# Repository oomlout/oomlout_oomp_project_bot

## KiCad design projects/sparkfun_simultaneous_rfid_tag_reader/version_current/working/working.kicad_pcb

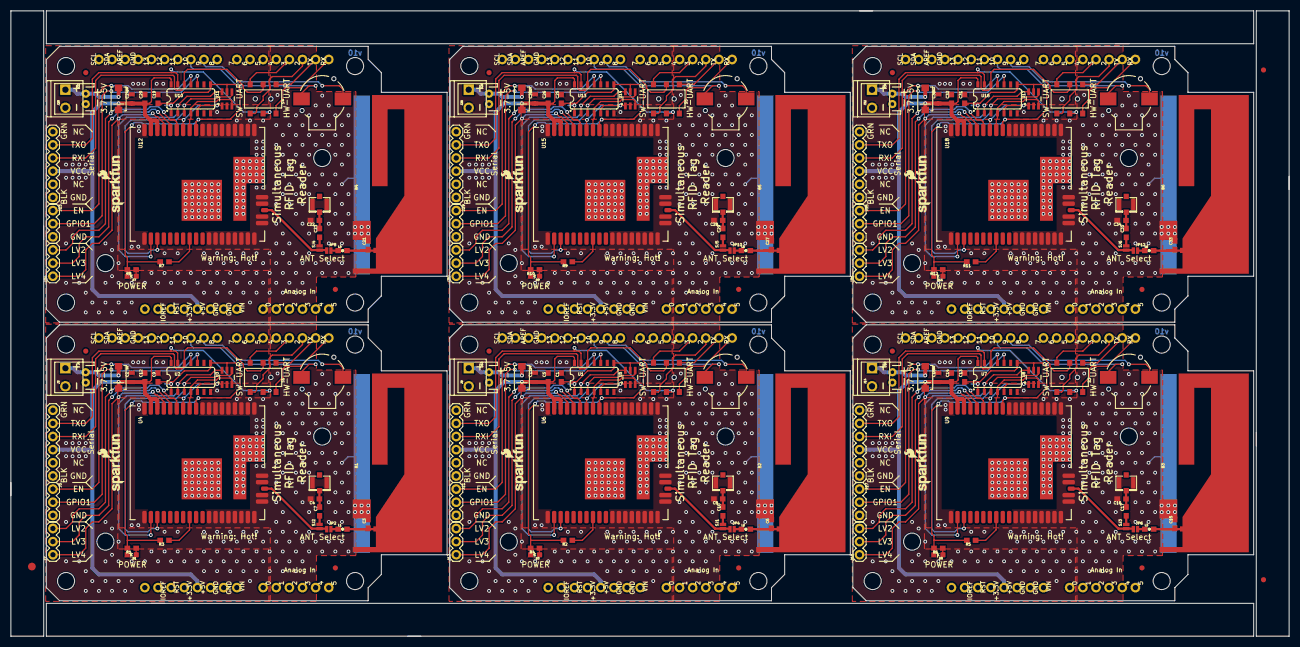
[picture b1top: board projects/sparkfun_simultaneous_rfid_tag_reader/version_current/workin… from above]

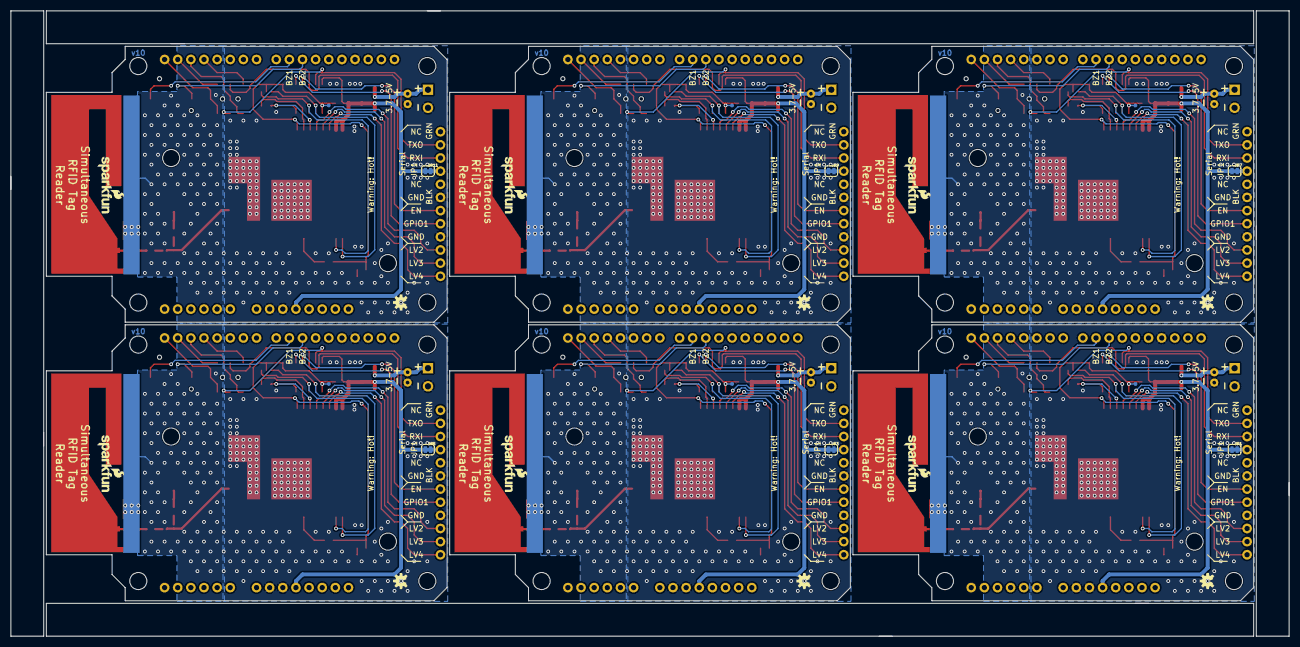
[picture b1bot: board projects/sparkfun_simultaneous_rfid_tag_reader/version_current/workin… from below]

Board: 2 copper layers, 247.1 x 120.9 mm, 237 parts (24 on the bottom side), 174 nets.

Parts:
B1, B2, B3, B4, B5, B6: ARDUINO_UNO_SHIELD; UNO_R3_SHIELD
C1, C5, C9, C12, C13, C14, C19, C20, C25, C26, C31, C32: 0.1uF; 0603
C2, C11, C18, C24, C30, C36: 10uF; 0805
C3, C6, C15, C21, C27, C33: DNP; 0603
C4, C7, C8, C10, C16, C17, C22, C23, C28, C29, C34, C35: TBD; 0603
D1, D3, D5, D7, D9, D11: RED; LED-0603
D2, D4, D6, D8, D10, D12: B340A; SMA-DIODE
E1, E2, E3, E4, E5, E6: Trace Antenna; 915MHZ_ANTENNA_TRIMBLE
E$1: FIDUCIAL-1.5X3
E$7, E$8: FIDUCIAL-1X2
FID1, FID2, FID3, FID4, FID5, FID6, FID7, FID8, FID9, FID10, FID11, FID12: FIDUCIAL1X2; FIDUCIAL-1X2
J1, J2, J13, J19, J25, J31: FTDI; 1X06
J3, J8, J14, J20, J26, J32: JST; JST-2-PTH
J4, J9, J15, J21, J27, J33: U.FL
J5, J11, J17, J23, J29, J35: Extra; 1X03
J6, J10, J16, J22, J28, J34: Screw Terminal; SCREWTERMINAL-3.5MM-2
J7, J12, J18, J24, J30, J36: GPIOs; 1X03
JP1, JP3, JP5, JP7, JP9, JP11: SMT-JUMPER_2_NC_TRACE_SILK
JP2, JP4, JP6, JP8, JP10, JP12: SJ1; SMT-JUMPER_2_NO_NO-SILK
L1, L2, L3, L4, L5, L6: 3.9nH; 0603
LOGO1, LOGO3, LOGO4, LOGO6, LOGO7, LOGO9, LOGO10, LOGO12, LOGO13, LOGO15, LOGO16, LOGO18: SFE_LOGO_NAME_FLAME.1_INCH; SFE_LOGO_NAME_FLAME_.1
LOGO2, LOGO5, LOGO8, LOGO11, LOGO14, LOGO17: OSHW-LOGOS; OSHW-LOGO-S
R1, R2, R3, R4, R5, R6, R7, R8, R9, R10, R11, R12: 1k; 0603
S1, S2, S3, S4, S5, S6: Serial Select; SWITCH_DPDT_SMD_AYZ0202
SG1, SG2, SG3, SG4, SG5, SG6: Buzzer; BUZZER-CCV
SJ1, SJ2, SJ3, SJ4, SJ5, SJ6: SMT-JUMPER_2_NO_NO-SILK
STANDOFF1, STANDOFF2, STANDOFF3, STANDOFF4, STANDOFF5, STANDOFF6, STANDOFF7, STANDOFF8, STANDOFF9, STANDOFF10, STANDOFF11, STANDOFF12, STANDOFF13, STANDOFF14, STANDOFF15, STANDOFF16, STANDOFF17, STANDOFF18, STANDOFF19, STANDOFF20, STANDOFF21, STANDOFF22, STANDOFF23, STANDOFF24, STANDOFF25, STANDOFF26, STANDOFF27, STANDOFF28, STANDOFF29, STANDOFF30, STANDOFF31, STANDOFF32, STANDOFF33, STANDOFF34, STANDOFF35, STANDOFF36: STAND-OFF
TP1, TP2, TP3, TP4, TP5, TP6: PAD.03X.03
U1, U2, U7, U10, U13, U16: TXB0104; SO14
U3, U5, U8, U11, U14, U17: ESD Diode; SOT-23-6
U4, U6, U9, U12, U15, U18: Nano; NANO_MODULE

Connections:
3.3V: C9.1, R1.2, R3.2, TP1.P$1, U2.1, U2.8, U3.5, U4.10
3.3V1: C1.1, R2.2, R4.2, TP2.P$1, U1.1, U1.8, U5.5, U6.10
3.3V2: C13.1, R5.2, R6.2, TP3.P$1, U7.1, U7.8, U8.5, U9.10
3.3V3: C19.1, R7.2, R8.2, TP4.P$1, U10.1, U10.8, U11.5, U12.10
3.3V4: C25.1, R9.2, R10.2, TP5.P$1, U13.1, U13.8, U14.5, U15.10
3.3V5: C31.1, R11.2, R12.2, TP6.P$1, U16.1, U16.8, U17.5, U18.10
ANT1: JP4.1, SJ1.1, U6.39
ANT2: JP6.1, SJ3.1, U9.39
ANT3: JP2.1, SJ2.1, U4.39
ANT4: JP8.1, SJ4.1, U12.39
ANT5: JP10.1, SJ5.1, U15.39
ANT6: JP12.1, SJ6.1, U18.39
ENABLE: J5.1, U2.11
ENABLE1: J11.1, U1.11
ENABLE2: J17.1, U7.11
ENABLE3: J23.1, U10.11
ENABLE4: J29.1, U13.11
ENABLE5: J35.1, U16.11
ENABLE-LV: U2.4, U3.3, U4.11
ENABLE-LV1: U1.4, U5.3, U6.11
ENABLE-LV2: U7.4, U8.3, U9.11
ENABLE-LV3: U10.4, U11.3, U12.11
ENABLE-LV4: U13.4, U14.3, U15.11
ENABLE-LV5: U16.4, U17.3, U18.11
GND: B1.GND@0, B1.GND@1, B1.GND@2, C2.2, C3.2, C4.2, C9.2, C12.2, D1.C, E1.GND@1, E1.GND@2, E1.GND@3, J2.1, J3.1, J4.P$1, J4.P$2, J5.3, J6.2, U2.7, U3.2, U4.1, U4.2, U4.3, U4.4, U4.5, U4.6, U4.7, U4.8, U4.9, U4.18, U4.19, U4.29, U4.30, U4.31, U4.32, U4.33, U4.34, U4.35, U4.36, U4.37, U4.38, U4.40, U4.41, U4.GND_PAD2
GND1: B2.GND@0, B2.GND@1, B2.GND@2, C1.2, C5.2, C6.2, C8.2, C11.2, D3.C, E2.GND@1, E2.GND@2, E2.GND@3, J1.1, J8.1, J9.P$1, J9.P$2, J10.2, J11.3, U1.7, U5.2, U6.1, U6.2, U6.3, U6.4, U6.5, U6.6, U6.7, U6.8, U6.9, U6.18, U6.19, U6.29, U6.30, U6.31, U6.32, U6.33, U6.34, U6.35, U6.36, U6.37, U6.38, U6.40, U6.41, U6.GND_PAD2
GND2: B3.GND@0, B3.GND@1, B3.GND@2, C13.2, C14.2, C15.2, C16.2, C18.2, D5.C, E3.GND@1, E3.GND@2, E3.GND@3, J13.1, J14.1, J15.P$1, J15.P$2, J16.2, J17.3, U7.7, U8.2, U9.1, U9.2, U9.3, U9.4, U9.5, U9.6, U9.7, U9.8, U9.9, U9.18, U9.19, U9.29, U9.30, U9.31, U9.32, U9.33, U9.34, U9.35, U9.36, U9.37, U9.38, U9.40, U9.41, U9.GND_PAD2
GND3: B4.GND@0, B4.GND@1, B4.GND@2, C19.2, C20.2, C21.2, C22.2, C24.2, D7.C, E4.GND@1, E4.GND@2, E4.GND@3, J19.1, J20.1, J21.P$1, J21.P$2, J22.2, J23.3, U10.7, U11.2, U12.1, U12.2, U12.3, U12.4, U12.5, U12.6, U12.7, U12.8, U12.9, U12.18, U12.19, U12.29, U12.30, U12.31, U12.32, U12.33, U12.34, U12.35, U12.36, U12.37, U12.38, U12.40, U12.41, U12.GND_PAD2
GND4: B5.GND@0, B5.GND@1, B5.GND@2, C25.2, C26.2, C27.2, C28.2, C30.2, D9.C, E5.GND@1, E5.GND@2, E5.GND@3, J25.1, J26.1, J27.P$1, J27.P$2, J28.2, J29.3, U13.7, U14.2, U15.1, U15.2, U15.3, U15.4, U15.5, U15.6, U15.7, U15.8, U15.9, U15.18, U15.19, U15.29, U15.30, U15.31, U15.32, U15.33, U15.34, U15.35, U15.36, U15.37, U15.38, U15.40, U15.41, U15.GND_PAD2
GND5: B6.GND@0, B6.GND@1, B6.GND@2, C31.2, C32.2, C33.2, C34.2, C36.2, D11.C, E6.GND@1, E6.GND@2, E6.GND@3, J31.1, J32.1, J33.P$1, J33.P$2, J34.2, J35.3, U16.7, U17.2, U18.1, U18.2, U18.3, U18.4, U18.5, U18.6, U18.7, U18.8, U18.9, U18.18, U18.19, U18.29, U18.30, U18.31, U18.32, U18.33, U18.34, U18.35, U18.36, U18.37, U18.38, U18.40, U18.41, U18.GND_PAD2
GPIO1: J5.2, U2.10
GPIO1-LV: U2.5, U3.1, U4.12
GPIO1-LV1: U1.5, U5.1, U6.12
GPIO1-LV2: U7.5, U8.1, U9.12
GPIO1-LV3: U10.5, U11.1, U12.12
GPIO1-LV4: U13.5, U14.1, U15.12
GPIO1-LV5: U16.5, U17.1, U18.12
GPIO2: J11.2, U1.10
GPIO2-LV: J7.3, U4.13
GPIO2-LV1: J12.3, U6.13
GPIO2-LV2: J18.3, U9.13
GPIO2-LV3: J24.3, U12.13
GPIO2-LV4: J30.3, U15.13
GPIO2-LV5: J36.3, U18.13
GPIO3: J17.2, U7.10
GPIO3-LV: J7.2, U4.14
GPIO3-LV1: J12.2, U6.14
GPIO3-LV2: J18.2, U9.14
GPIO3-LV3: J24.2, U12.14
GPIO3-LV4: J30.2, U15.14
GPIO3-LV5: J36.2, U18.14
GPIO4: J23.2, U10.10
GPIO4-LV: J7.1, U4.15
GPIO4-LV1: J12.1, U6.15
GPIO4-LV2: J18.1, U9.15
GPIO4-LV3: J24.1, U12.15
GPIO4-LV4: J30.1, U15.15
GPIO4-LV5: J36.1, U18.15
GPIO5: J29.2, U13.10
GPIO6: J35.2, U16.10
unnamed: C3.1, E1.ANT, L1.2
unnamed: JP2.2, L1.1
unnamed: C7.1, SJ2.2
unnamed: R3.1, U4.26
unnamed: C4.1, C7.2, J4.P$3
unnamed: D1.A, R1.1
unnamed: J2.3, JP1.2
unnamed: B1.RX, S1.1
unnamed: B1.TX, S1.4
unnamed: B1.D9, SG1.+
unnamed: D2.A, J3.2, J6.1
unnamed: B1.D10, SG1.-
unnamed: R2.1, U6.26
unnamed: B2.RX, S2.1
unnamed: B2.TX, S2.4
unnamed: C6.1, E2.ANT, L2.2
unnamed: JP4.2, L2.1
unnamed: C10.1, SJ1.2
unnamed: C8.1, C10.2, J9.P$3
unnamed: D3.A, R4.1
unnamed: J1.3, JP3.2
unnamed: D4.A, J8.2, J10.1
unnamed: B2.D9, SG2.+
unnamed: B2.D10, SG2.-
unnamed: R5.1, U9.26
unnamed: B3.RX, S3.1
unnamed: B3.TX, S3.4
unnamed: C15.1, E3.ANT, L3.2
unnamed: JP6.2, L3.1
unnamed: C17.1, SJ3.2
unnamed: C16.1, C17.2, J15.P$3
unnamed: D5.A, R6.1
unnamed: J13.3, JP5.2
unnamed: D6.A, J14.2, J16.1
unnamed: B3.D9, SG3.+
unnamed: B3.D10, SG3.-
unnamed: R7.1, U12.26
unnamed: B4.RX, S4.1
unnamed: B4.TX, S4.4
unnamed: C21.1, E4.ANT, L4.2
unnamed: JP8.2, L4.1
unnamed: C23.1, SJ4.2
unnamed: C22.1, C23.2, J21.P$3
unnamed: D7.A, R8.1
unnamed: J19.3, JP7.2
unnamed: D8.A, J20.2, J22.1
unnamed: B4.D9, SG4.+
unnamed: B4.D10, SG4.-
unnamed: R9.1, U15.26
unnamed: B5.RX, S5.1
unnamed: B5.TX, S5.4
unnamed: C27.1, E5.ANT, L5.2
unnamed: JP10.2, L5.1
unnamed: C29.1, SJ5.2
unnamed: C28.1, C29.2, J27.P$3
unnamed: D9.A, R10.1
unnamed: J25.3, JP9.2
unnamed: D10.A, J26.2, J28.1
unnamed: B5.D9, SG5.+
unnamed: B5.D10, SG5.-
unnamed: R11.1, U18.26
unnamed: B6.RX, S6.1
unnamed: B6.TX, S6.4
unnamed: C33.1, E6.ANT, L6.2
unnamed: JP12.2, L6.1
unnamed: C35.1, SJ6.2
unnamed: C34.1, C35.2, J33.P$3
unnamed: D11.A, R12.1
unnamed: J31.3, JP11.2
unnamed: D12.A, J32.2, J34.1
unnamed: B6.D9, SG6.+
unnamed: B6.D10, SG6.-
RXI: J2.4, S1.5, U2.12
RXI1: J1.4, S2.5, U1.12
RXI2: J13.4, S3.5, U7.12
RXI3: J19.4, S4.5, U10.12
RXI4: J25.4, S5.5, U13.12
RXI5: J31.4, S6.5, U16.12
RXI-LV: U2.3, U3.4, U4.21
RXI-LV1: U1.3, U5.4, U6.21
RXI-LV2: U7.3, U8.4, U9.21
RXI-LV3: U10.3, U11.4, U12.21
RXI-LV4: U13.3, U14.4, U15.21
RXI-LV5: U16.3, U17.4, U18.21
SOFT-RX: B1.D2, S1.3
SOFT-RX1: B2.D2, S2.3
SOFT-RX2: B3.D2, S3.3
SOFT-RX3: B4.D2, S4.3
SOFT-RX4: B5.D2, S5.3
SOFT-RX5: B6.D2, S6.3
SOFT-TX: B1.D3, S1.6
SOFT-TX1: B2.D3, S2.6
SOFT-TX2: B3.D3, S3.6
SOFT-TX3: B4.D3, S4.6
SOFT-TX4: B5.D3, S5.6
SOFT-TX5: B6.D3, S6.6
TXO: J2.5, S1.2, U2.13
TXO1: J1.5, S2.2, U1.13
TXO2: J13.5, S3.2, U7.13
TXO3: J19.5, S4.2, U10.13
TXO4: J25.5, S5.2, U13.13
TXO5: J31.5, S6.2, U16.13
TXO-LV: U2.2, U3.6, U4.20
TXO-LV1: U1.2, U5.6, U6.20
TXO-LV2: U7.2, U8.6, U9.20
TXO-LV3: U10.2, U11.6, U12.20
TXO-LV4: U13.2, U14.6, U15.20
TXO-LV5: U16.2, U17.6, U18.20
VCC: B1.5V, C2.1, C12.1, D2.C, JP1.1, U2.14, U4.16, U4.17
VCC1: B2.5V, C5.1, C11.1, D4.C, JP3.1, U1.14, U6.16, U6.17
VCC2: B3.5V, C14.1, C18.1, D6.C, JP5.1, U7.14, U9.16, U9.17
VCC3: B4.5V, C20.1, C24.1, D8.C, JP7.1, U10.14, U12.16, U12.17
VCC4: B5.5V, C26.1, C30.1, D10.C, JP9.1, U13.14, U15.16, U15.17
VCC5: B6.5V, C32.1, C36.1, D12.C, JP11.1, U16.14, U18.16, U18.17

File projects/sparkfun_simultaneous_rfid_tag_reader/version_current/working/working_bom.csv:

"Id";"Designator";"Footprint";"Quantity";"Designation";"Supplier and ref";
1;"STANDOFF33,STANDOFF18,STANDOFF16,STANDOFF35,STANDOFF25,STANDOFF14,STANDOFF5,STANDOFF8,STANDOFF10,STANDOFF26,STANDOFF28,STANDOFF13,STANDOFF7,STANDOFF3,STANDOFF32,STANDOFF9,STANDOFF21,STANDOFF4,STANDOFF20,STANDOFF19,STANDOFF6,STANDOFF24,STANDOFF34,STANDOFF29,STANDOFF23,STANDOFF22,STANDOFF36,STANDOFF2,STANDOFF17,STANDOFF27,STANDOFF31,STANDOFF30,STANDOFF11,STANDOFF1,STANDOFF15,STANDOFF12";"STAND-OFF";36;"STAND-OFF";;;
2;"S3,S5,S4,S6,S1,S2";"SWITCH_DPDT_SMD_AYZ0202";6;"Serial Select";;;
3;"SJ4,SJ1,SJ3,SJ2,SJ5,SJ6";"SMT-JUMPER_2_NO_NO-SILK";6;"";;;
4;"FID10,FID2,FID6,FID11,FID7,FID12,FID5,FID9,FID8,FID1,FID3,FID4";"FIDUCIAL-1X2";12;"FIDUCIAL1X2";;;
5;"C2,C24,C11,C30,C36,C18";"0805";6;"10uF";;;
6;"C26,C12,C5,C20,C19,C1,C14,C31,C9,C25,C13,C32";"0603";12;"0.1uF";;;
7;"J33,J9,J15,J4,J21,J27";"U.FL";6;"U.FL";;;
8;"C8,C17,C10,C29,C7,C34,C23,C4,C22,C16,C28,C35";"0603";12;"TBD";;;
9;"J30,J24,J7,J12,J36,J18";"1X03";6;"GPIOs";;;
10;"J14,J26,J32,J3,J20,J8";"JST-2-PTH";6;"JST";;;
11;"R6,R1,R11,R8,R7,R3,R4,R10,R9,R2,R5,R12";"0603";12;"1k";;;
12;"C15,C33,C21,C3,C6,C27";"0603";6;"DNP";;;
13;"U10,U16,U13,U7,U2,U1";"SO14";6;"TXB0104";;;
14;"J25,J13,J1,J2,J19,J31";"1X06";6;"FTDI";;;
15;"JP2,JP4,JP6,JP10,JP12,JP8";"SMT-JUMPER_2_NO_NO-SILK";6;"SJ1";;;
16;"B6,B3,B2,B4,B5,B1";"UNO_R3_SHIELD";6;"ARDUINO_UNO_SHIELD";;;
17;"LOGO16,LOGO10,LOGO7,LOGO13,LOGO1,LOGO4,LOGO9,LOGO6,LOGO15,LOGO12,LOGO3,LOGO18";"SFE_LOGO_NAME_FLAME_.1";12;"SFE_LOGO_NAME_FLAME.1_INCH";;;
18;"D9,D5,D11,D1,D7,D3";"LED-0603";6;"RED";;;
19;"E5,E2,E6,E1,E3,E4";"915MHZ_ANTENNA_TRIMBLE";6;"Trace Antenna";;;
20;"D8,D10,D2,D4,D12,D6";"SMA-DIODE";6;"B340A";;;
21;"J17,J5,J29,J23,J11,J35";"1X03";6;"Extra";;;
22;"L4,L1,L3,L6,L2,L5";"0603";6;"3.9nH";;;
23;"U6,U15,U9,U18,U4,U12";"NANO_MODULE";6;"Nano";;;
24;"E$8,E$7";"FIDUCIAL-1X2";2;"";;;
25;"SG5,SG3,SG1,SG4,SG2,SG6";"BUZZER-CCV";6;"Buzzer";;;
26;"U3,U17,U8,U14,U11,U5";"SOT-23-6";6;"ESD Diode";;;
27;"J22,J16,J34,J10,J28,J6";"SCREWTERMINAL-3.5MM-2";6;"Screw Terminal";;;
28;"E$1";"FIDUCIAL-1.5X3";1;"";;;
29;"LOGO17,LOGO14,LOGO2,LOGO8,LOGO11,LOGO5";"OSHW-LOGO-S";6;"OSHW-LOGOS";;;
30;"TP5,TP2,TP1,TP6,TP4,TP3";"PAD.03X.03";6;"";;;
31;"JP7,JP9,JP1,JP3,JP11,JP5";"SMT-JUMPER_2_NC_TRACE_SILK";6;"";;;

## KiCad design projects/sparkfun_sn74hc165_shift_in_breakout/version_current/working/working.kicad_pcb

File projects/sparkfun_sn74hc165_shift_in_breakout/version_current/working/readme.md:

# SN74HC165-Shift-In-Breakout by sparkfun  
This is a harvested standardized copy of a project from github.  
The original project can be found at:  
https://github.com/sparkfun/SN74HC165-Shift-In-Breakout  
Please consult that link for additional, details, files, and license information.  
Note: It was auto harvested and if the original repo had more than one board file or anything out of the ordinary the files here are likely not representative.

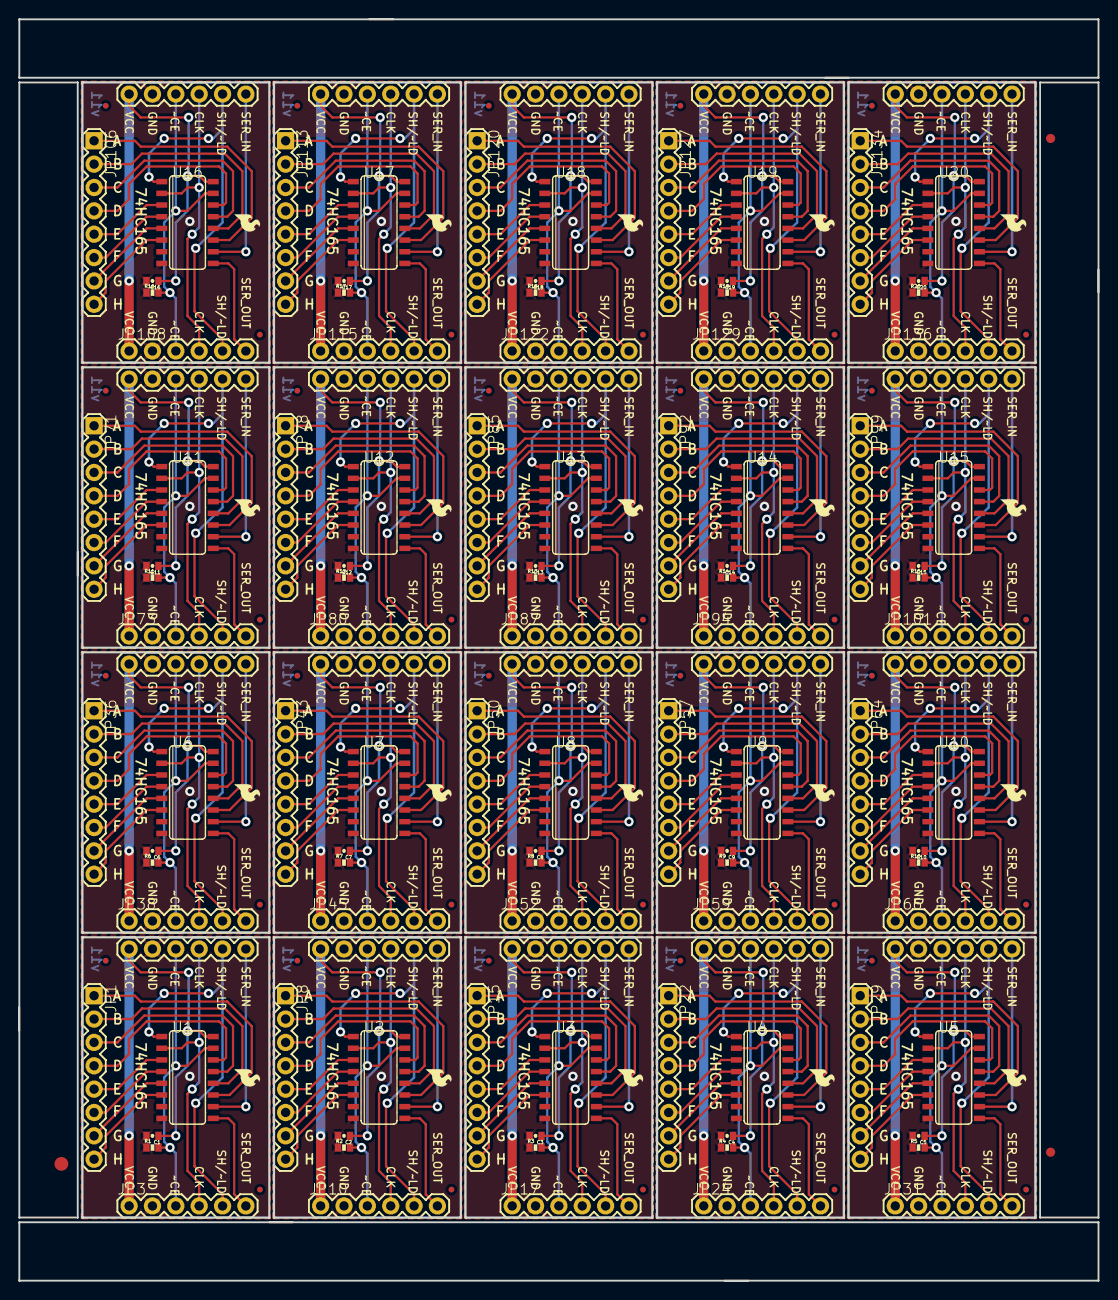
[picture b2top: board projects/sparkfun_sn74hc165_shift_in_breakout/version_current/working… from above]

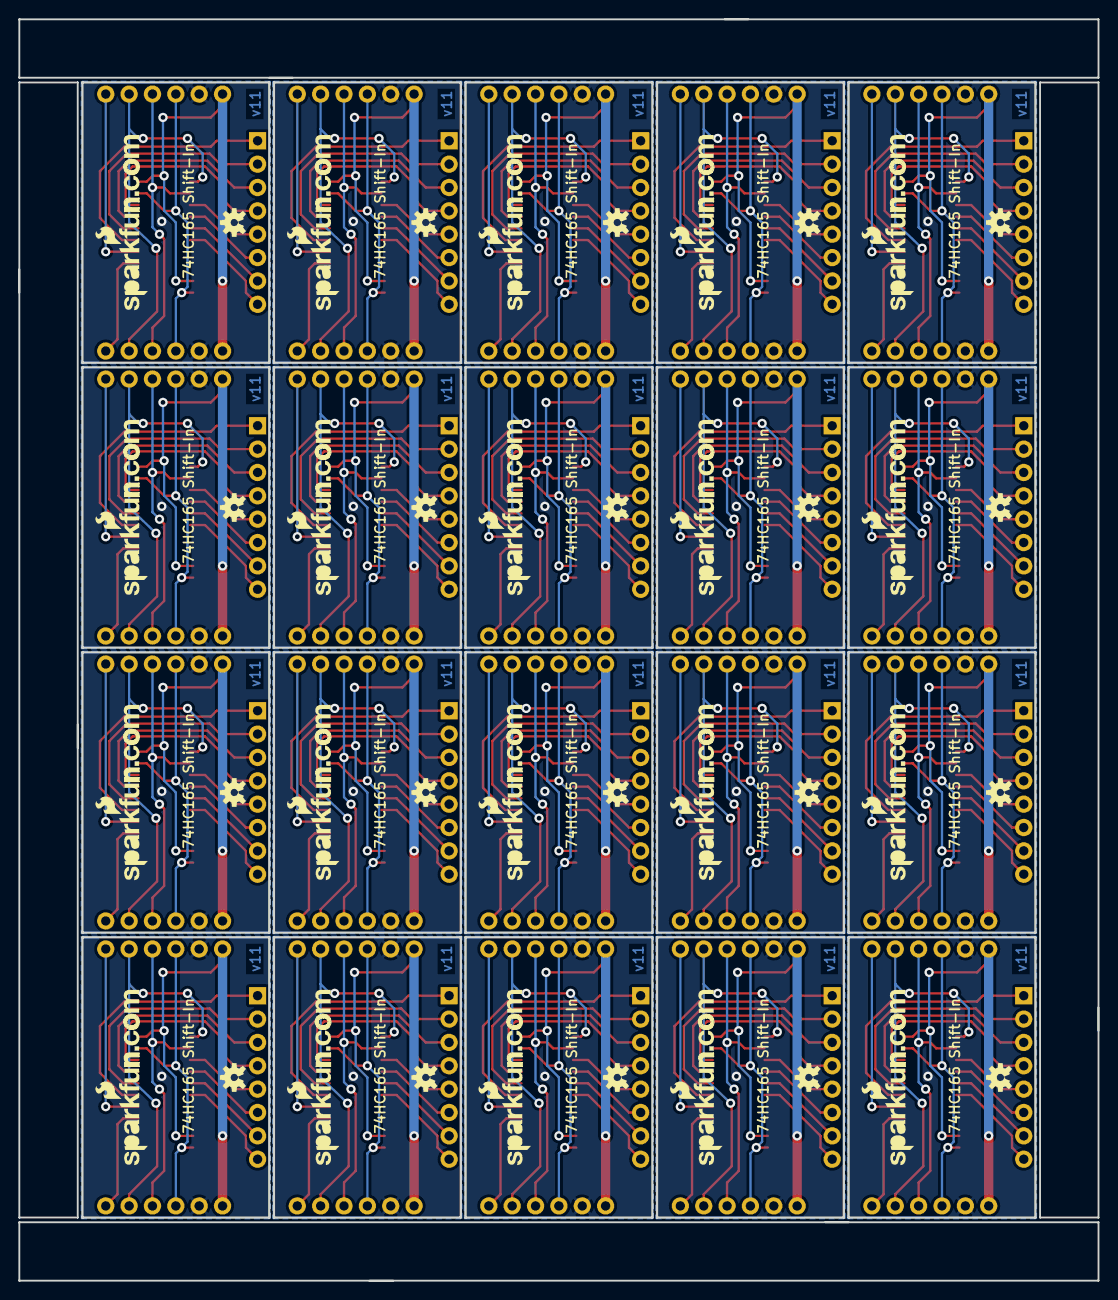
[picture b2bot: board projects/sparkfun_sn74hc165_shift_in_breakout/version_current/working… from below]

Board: 2 copper layers, 117.3 x 137.2 mm, 223 parts (40 on the bottom side), 300 nets.

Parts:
C1, C2, C3, C4, C5, C6, C7, C8, C9, C10, C11, C12, C13, C14, C15, C16, C17, C18, C19, C20: .1uF; 0402-CAP
E$1: FIDUCIAL-1.5X3
E$7, E$8: FIDUCIAL-1X2
JP1, JP8, JP15, JP22, JP29, JP36, JP43, JP50, JP57, JP64, JP71, JP78, JP85, JP92, JP99, JP106, JP113, JP120, JP127, JP134: 1X08
JP2, JP3, JP9, JP10, JP16, JP17, JP23, JP24, JP30, JP31, JP37, JP38, JP44, JP45, JP51, JP52, JP58, JP59, JP65, JP66, JP72, JP73, JP79, JP80, JP86, JP87, JP93, JP94, JP100, JP101, JP107, JP108, JP114, JP115, JP121, JP122, JP128, JP129, JP135, JP136: 1X06
JP4, JP11, JP18, JP25, JP32, JP39, JP46, JP53, JP60, JP67, JP74, JP81, JP88, JP95, JP102, JP109, JP116, JP123, JP130, JP137: LOGO-SFESK; SFE-LOGO-FLAME
JP5, JP12, JP19, JP26, JP33, JP40, JP47, JP54, JP61, JP68, JP75, JP82, JP89, JP96, JP103, JP110, JP117, JP124, JP131, JP138: LOGO-SFENEW; SFE-NEW-WEBLOGO
JP6, JP7, JP13, JP14, JP20, JP21, JP27, JP28, JP34, JP35, JP41, JP42, JP48, JP49, JP55, JP56, JP62, JP63, JP69, JP70, JP76, JP77, JP83, JP84, JP90, JP91, JP97, JP98, JP104, JP105, JP111, JP112, JP118, JP119, JP125, JP126, JP132, JP133, JP139, JP140: FIDUCIALUFIDUCIAL; MICRO-FIDUCIAL
R1, R2, R3, R4, R5, R6, R7, R8, R9, R10, R11, R12, R13, R14, R15, R16, R17, R18, R19, R20: 10k; 0402-RES
U1, U2, U3, U4, U5, U6, U7, U8, U9, U10, U11, U12, U13, U14, U15, U16, U17, U18, U19, U20: 74HC165D; SO16
U$1, U$2, U$3, U$4, U$5, U$6, U$7, U$8, U$9, U$10, U$11, U$12, U$13, U$14, U$15, U$16, U$17, U$18, U$19, U$20: OSHW-LOGOS; OSHW-LOGO-S

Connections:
A: JP1.1, U1.11
A1: JP8.1, U2.11
A2: JP15.1, U3.11
A3: JP22.1, U4.11
A4: JP29.1, U5.11
A5: JP36.1, U6.11
A6: JP43.1, U7.11
A7: JP50.1, U8.11
A8: JP57.1, U9.11
A9: JP64.1, U10.11
A10: JP71.1, U11.11
A11: JP78.1, U12.11
A12: JP85.1, U13.11
A13: JP92.1, U14.11
A14: JP99.1, U15.11
A15: JP106.1, U16.11
A16: JP113.1, U17.11
A17: JP120.1, U18.11
A18: JP127.1, U19.11
A19: JP134.1, U20.11
B: JP1.2, U1.12
B1: JP8.2, U2.12
B2: JP15.2, U3.12
B3: JP22.2, U4.12
B4: JP29.2, U5.12
B5: JP36.2, U6.12
B6: JP43.2, U7.12
B7: JP50.2, U8.12
B8: JP57.2, U9.12
B9: JP64.2, U10.12
B10: JP71.2, U11.12
B11: JP78.2, U12.12
B12: JP85.2, U13.12
B13: JP92.2, U14.12
B14: JP99.2, U15.12
B15: JP106.2, U16.12
B16: JP113.2, U17.12
B17: JP120.2, U18.12
B18: JP127.2, U19.12
B19: JP134.2, U20.12
C: JP1.3, U1.13
C1: JP8.3, U2.13
C2: JP15.3, U3.13
C3: JP22.3, U4.13
C4: JP29.3, U5.13
C5: JP36.3, U6.13
C6: JP43.3, U7.13
C7: JP50.3, U8.13
C8: JP57.3, U9.13
C9: JP64.3, U10.13
C10: JP71.3, U11.13
C11: JP78.3, U12.13
C12: JP85.3, U13.13
C13: JP92.3, U14.13
C14: JP99.3, U15.13
C15: JP106.3, U16.13
C16: JP113.3, U17.13
C17: JP120.3, U18.13
C18: JP127.3, U19.13
C19: JP134.3, U20.13
CLK: JP2.4, JP3.4, U1.2
CLK1: JP9.4, JP10.4, U2.2
CLK2: JP16.4, JP17.4, U3.2
CLK3: JP23.4, JP24.4, U4.2
CLK4: JP30.4, JP31.4, U5.2
CLK5: JP37.4, JP38.4, U6.2
CLK6: JP44.4, JP45.4, U7.2
CLK7: JP51.4, JP52.4, U8.2
CLK8: JP58.4, JP59.4, U9.2
CLK9: JP65.4, JP66.4, U10.2
CLK10: JP72.4, JP73.4, U11.2
CLK11: JP79.4, JP80.4, U12.2
CLK12: JP86.4, JP87.4, U13.2
CLK13: JP93.4, JP94.4, U14.2
CLK14: JP100.4, JP101.4, U15.2
CLK15: JP107.4, JP108.4, U16.2
CLK16: JP114.4, JP115.4, U17.2
CLK17: JP121.4, JP122.4, U18.2
CLK18: JP128.4, JP129.4, U19.2
CLK19: JP135.4, JP136.4, U20.2
D: JP1.4, U1.14
D1: JP8.4, U2.14
D2: JP15.4, U3.14
D3: JP22.4, U4.14
D4: JP29.4, U5.14
D5: JP36.4, U6.14
D6: JP43.4, U7.14
D7: JP50.4, U8.14
D8: JP57.4, U9.14
D9: JP64.4, U10.14
D10: JP71.4, U11.14
D11: JP78.4, U12.14
D12: JP85.4, U13.14
D13: JP92.4, U14.14
D14: JP99.4, U15.14
D15: JP106.4, U16.14
D16: JP113.4, U17.14
D17: JP120.4, U18.14
D18: JP127.4, U19.14
D19: JP134.4, U20.14
E: JP1.5, U1.3
E1: JP8.5, U2.3
E2: JP15.5, U3.3
E3: JP22.5, U4.3
E4: JP29.5, U5.3
E5: JP36.5, U6.3
E6: JP43.5, U7.3
E7: JP50.5, U8.3
E8: JP57.5, U9.3
E9: JP64.5, U10.3
E10: JP71.5, U11.3
E11: JP78.5, U12.3
E12: JP85.5, U13.3
E13: JP92.5, U14.3
E14: JP99.5, U15.3
E15: JP106.5, U16.3
E16: JP113.5, U17.3
E17: JP120.5, U18.3
E18: JP127.5, U19.3
E19: JP134.5, U20.3
F: JP1.6, U1.4
F1: JP8.6, U2.4
F2: JP15.6, U3.4
F3: JP22.6, U4.4
F4: JP29.6, U5.4
F5: JP36.6, U6.4
F6: JP43.6, U7.4
F7: JP50.6, U8.4
F8: JP57.6, U9.4
F9: JP64.6, U10.4
F10: JP71.6, U11.4
F11: JP78.6, U12.4
F12: JP85.6, U13.4
F13: JP92.6, U14.4
F14: JP99.6, U15.4
F15: JP106.6, U16.4
F16: JP113.6, U17.4
F17: JP120.6, U18.4
F18: JP127.6, U19.4
F19: JP134.6, U20.4
G: JP1.7, U1.5
G1: JP8.7, U2.5
G2: JP15.7, U3.5
G3: JP22.7, U4.5
G4: JP29.7, U5.5
G5: JP36.7, U6.5
G6: JP43.7, U7.5
G7: JP50.7, U8.5
G8: JP57.7, U9.5
G9: JP64.7, U10.5
G10: JP71.7, U11.5
G11: JP78.7, U12.5
G12: JP85.7, U13.5
G13: JP92.7, U14.5
G14: JP99.7, U15.5
G15: JP106.7, U16.5
G16: JP113.7, U17.5
G17: JP120.7, U18.5
G18: JP127.7, U19.5
G19: JP134.7, U20.5
GND: C1.2, JP2.2, JP3.2, R1.1, U1.8
GND1: C2.2, JP9.2, JP10.2, R2.1, U2.8
GND2: C3.2, JP16.2, JP17.2, R3.1, U3.8
GND3: C4.2, JP23.2, JP24.2, R4.1, U4.8
GND4: C5.2, JP30.2, JP31.2, R5.1, U5.8
GND5: C6.2, JP37.2, JP38.2, R6.1, U6.8
GND6: C7.2, JP44.2, JP45.2, R7.1, U7.8
GND7: C8.2, JP51.2, JP52.2, R8.1, U8.8
GND8: C9.2, JP58.2, JP59.2, R9.1, U9.8
GND9: C10.2, JP65.2, JP66.2, R10.1, U10.8
GND10: C11.2, JP72.2, JP73.2, R11.1, U11.8
GND11: C12.2, JP79.2, JP80.2, R12.1, U12.8
GND12: C13.2, JP86.2, JP87.2, R13.1, U13.8
GND13: C14.2, JP93.2, JP94.2, R14.1, U14.8
GND14: C15.2, JP100.2, JP101.2, R15.1, U15.8
GND15: C16.2, JP107.2, JP108.2, R16.1, U16.8
GND16: C17.2, JP114.2, JP115.2, R17.1, U17.8
GND17: C18.2, JP121.2, JP122.2, R18.1, U18.8
GND18: C19.2, JP128.2, JP129.2, R19.1, U19.8
GND19: C20.2, JP135.2, JP136.2, R20.1, U20.8
H: JP1.8, U1.6
H1: JP8.8, U2.6
H2: JP15.8, U3.6
H3: JP22.8, U4.6
H4: JP29.8, U5.6
H5: JP36.8, U6.6
H6: JP43.8, U7.6
H7: JP50.8, U8.6
H8: JP57.8, U9.6
H9: JP64.8, U10.6
H10: JP71.8, U11.6
H11: JP78.8, U12.6
H12: JP85.8, U13.6
H13: JP92.8, U14.6
H14: JP99.8, U15.6
H15: JP106.8, U16.6
H16: JP113.8, U17.6
H17: JP120.8, U18.6
H18: JP127.8, U19.6
H19: JP134.8, U20.6
SERIAL_IN: JP2.6, U1.10
SERIAL_IN1: JP9.6, U2.10
SERIAL_IN2: JP16.6, U3.10
SERIAL_IN3: JP23.6, U4.10
SERIAL_IN4: JP30.6, U5.10
SERIAL_IN5: JP37.6, U6.10
SERIAL_IN6: JP44.6, U7.10
SERIAL_IN7: JP51.6, U8.10
SERIAL_IN8: JP58.6, U9.10
SERIAL_IN9: JP65.6, U10.10
SERIAL_IN10: JP72.6, U11.10
SERIAL_IN11: JP79.6, U12.10
SERIAL_IN12: JP86.6, U13.10
SERIAL_IN13: JP93.6, U14.10
SERIAL_IN14: JP100.6, U15.10
SERIAL_IN15: JP107.6, U16.10
SERIAL_IN16: JP114.6, U17.10
SERIAL_IN17: JP121.6, U18.10
SERIAL_IN18: JP128.6, U19.10
SERIAL_IN19: JP135.6, U20.10
SERIAL_OUT: JP3.6, U1.9
SERIAL_OUT1: JP10.6, U2.9
SERIAL_OUT2: JP17.6, U3.9
SERIAL_OUT3: JP24.6, U4.9
SERIAL_OUT4: JP31.6, U5.9
SERIAL_OUT5: JP38.6, U6.9
SERIAL_OUT6: JP45.6, U7.9
SERIAL_OUT7: JP52.6, U8.9
SERIAL_OUT8: JP59.6, U9.9
SERIAL_OUT9: JP66.6, U10.9
SERIAL_OUT10: JP73.6, U11.9
SERIAL_OUT11: JP80.6, U12.9
SERIAL_OUT12: JP87.6, U13.9
SERIAL_OUT13: JP94.6, U14.9
SERIAL_OUT14: JP101.6, U15.9
SERIAL_OUT15: JP108.6, U16.9
SERIAL_OUT16: JP115.6, U17.9
SERIAL_OUT17: JP122.6, U18.9
SERIAL_OUT18: JP129.6, U19.9
SERIAL_OUT19: JP136.6, U20.9
SHIFT/~LOAD1: JP9.5, JP10.5, U2.1
SHIFT/~LOAD2: JP16.5, JP17.5, U3.1
SHIFT/~LOAD3: JP23.5, JP24.5, U4.1
SHIFT/~LOAD4: JP30.5, JP31.5, U5.1
SHIFT/~LOAD5: JP37.5, JP38.5, U6.1
SHIFT/~LOAD6: JP44.5, JP45.5, U7.1
SHIFT/~LOAD7: JP51.5, JP52.5, U8.1
SHIFT/~LOAD8: JP58.5, JP59.5, U9.1
SHIFT/~LOAD9: JP65.5, JP66.5, U10.1
SHIFT/~LOAD10: JP72.5, JP73.5, U11.1
SHIFT/~LOAD11: JP79.5, JP80.5, U12.1
SHIFT/~LOAD12: JP86.5, JP87.5, U13.1
SHIFT/~LOAD13: JP93.5, JP94.5, U14.1
SHIFT/~LOAD14: JP100.5, JP101.5, U15.1
SHIFT/~LOAD15: JP107.5, JP108.5, U16.1
SHIFT/~LOAD16: JP114.5, JP115.5, U17.1
SHIFT/~LOAD17: JP121.5, JP122.5, U18.1
SHIFT/~LOAD18: JP128.5, JP129.5, U19.1
SHIFT/~LOAD19: JP135.5, JP136.5, U20.1
SHIFT/~LOAD: JP2.5, JP3.5, U1.1
VCC: C1.1, JP2.1, JP3.1, U1.16
VCC1: C2.1, JP9.1, JP10.1, U2.16
VCC2: C3.1, JP16.1, JP17.1, U3.16
VCC3: C4.1, JP23.1, JP24.1, U4.16
VCC4: C5.1, JP30.1, JP31.1, U5.16
VCC5: C6.1, JP37.1, JP38.1, U6.16
VCC6: C7.1, JP44.1, JP45.1, U7.16
VCC7: C8.1, JP51.1, JP52.1, U8.16
VCC8: C9.1, JP58.1, JP59.1, U9.16
VCC9: C10.1, JP65.1, JP66.1, U10.16
VCC10: C11.1, JP72.1, JP73.1, U11.16
VCC11: C12.1, JP79.1, JP80.1, U12.16
VCC12: C13.1, JP86.1, JP87.1, U13.16
VCC13: C14.1, JP93.1, JP94.1, U14.16
VCC14: C15.1, JP100.1, JP101.1, U15.16
VCC15: C16.1, JP107.1, JP108.1, U16.16
VCC16: C17.1, JP114.1, JP115.1, U17.16
VCC17: C18.1, JP121.1, JP122.1, U18.16
VCC18: C19.1, JP128.1, JP129.1, U19.16
VCC19: C20.1, JP135.1, JP136.1, U20.16
~CLK_ENABLE1: JP9.3, JP10.3, R2.2, U2.15
~CLK_ENABLE2: JP16.3, JP17.3, R3.2, U3.15
~CLK_ENABLE3: JP23.3, JP24.3, R4.2, U4.15
~CLK_ENABLE4: JP30.3, JP31.3, R5.2, U5.15
~CLK_ENABLE5: JP37.3, JP38.3, R6.2, U6.15
~CLK_ENABLE6: JP44.3, JP45.3, R7.2, U7.15
~CLK_ENABLE7: JP51.3, JP52.3, R8.2, U8.15
~CLK_ENABLE8: JP58.3, JP59.3, R9.2, U9.15
~CLK_ENABLE9: JP65.3, JP66.3, R10.2, U10.15
~CLK_ENABLE10: JP72.3, JP73.3, R11.2, U11.15
~CLK_ENABLE11: JP79.3, JP80.3, R12.2, U12.15
~CLK_ENABLE12: JP86.3, JP87.3, R13.2, U13.15
~CLK_ENABLE13: JP93.3, JP94.3, R14.2, U14.15
~CLK_ENABLE14: JP100.3, JP101.3, R15.2, U15.15
~CLK_ENABLE15: JP107.3, JP108.3, R16.2, U16.15
~CLK_ENABLE16: JP114.3, JP115.3, R17.2, U17.15
~CLK_ENABLE17: JP121.3, JP122.3, R18.2, U18.15
~CLK_ENABLE18: JP128.3, JP129.3, R19.2, U19.15
~CLK_ENABLE19: JP135.3, JP136.3, R20.2, U20.15
~CLK_ENABLE: JP2.3, JP3.3, R1.2, U1.15

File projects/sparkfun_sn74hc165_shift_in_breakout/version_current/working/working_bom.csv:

"Id";"Designator";"Footprint";"Quantity";"Designation";"Supplier and ref";
1;"JP10,JP3,JP59,JP93,JP101,JP52,JP108,JP122,JP65,JP100,JP73,JP17,JP80,JP107,JP38,JP23,JP2,JP44,JP121,JP30,JP24,JP87,JP45,JP51,JP94,JP37,JP16,JP86,JP79,JP135,JP136,JP66,JP128,JP31,JP72,JP114,JP129,JP9,JP115,JP58";"1X06";40;"";;;
2;"JP20,JP21,JP77,JP7,JP27,JP48,JP6,JP63,JP105,JP13,JP97,JP55,JP69,JP104,JP125,JP56,JP111,JP42,JP126,JP84,JP76,JP83,JP112,JP90,JP34,JP91,JP132,JP139,JP62,JP119,JP70,JP98,JP133,JP49,JP35,JP118,JP140,JP28,JP14,JP41";"MICRO-FIDUCIAL";40;"FIDUCIALUFIDUCIAL";;;
3;"JP11,JP102,JP18,JP60,JP46,JP39,JP123,JP137,JP95,JP53,JP74,JP67,JP109,JP32,JP25,JP88,JP130,JP116,JP81,JP4";"SFE-LOGO-FLAME";20;"LOGO-SFESK";;;
4;"R10,R8,R19,R2,R14,R5,R12,R15,R20,R17,R9,R13,R7,R3,R16,R11,R1,R18,R6,R4";"0402-RES";20;"10k";;;
5;"JP127,JP8,JP78,JP64,JP36,JP50,JP15,JP22,JP134,JP57,JP71,JP99,JP92,JP29,JP85,JP120,JP43,JP113,JP1,JP106";"1X08";20;"";;;
6;"C5,C6,C1,C19,C4,C13,C9,C3,C2,C14,C10,C8,C15,C18,C11,C7,C20,C12,C16,C17";"0402-CAP";20;".1uF";;;
7;"E$7,E$8";"FIDUCIAL-1X2";2;"";;;
8;"U17,U20,U8,U16,U6,U15,U10,U12,U11,U19,U2,U3,U5,U13,U9,U7,U18,U1,U4,U14";"SO16";20;"74HC165D";;;
9;"E$1";"FIDUCIAL-1.5X3";1;"";;;
10;"U$18,U$15,U$12,U$16,U$11,U$19,U$13,U$5,U$1,U$9,U$2,U$10,U$4,U$7,U$3,U$17,U$6,U$14,U$20,U$8";"OSHW-LOGO-S";20;"OSHW-LOGOS";;;
11;"JP89,JP19,JP54,JP40,JP117,JP138,JP12,JP96,JP131,JP47,JP33,JP5,JP103,JP75,JP82,JP110,JP124,JP61,JP26,JP68";"SFE-NEW-WEBLOGO";20;"LOGO-SFENEW";;;

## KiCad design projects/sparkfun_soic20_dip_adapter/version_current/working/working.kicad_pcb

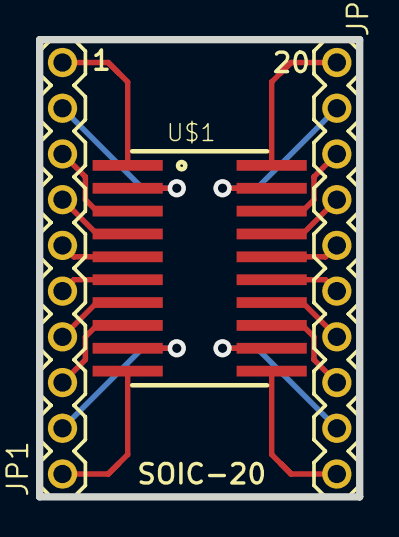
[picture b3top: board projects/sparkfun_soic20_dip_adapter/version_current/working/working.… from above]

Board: 16 copper layers, 17.8 x 25.4 mm, 4 parts (1 on the bottom side), 20 nets.

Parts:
JP1, JP2: M100.1; 1X10
U$1: SOIC_20; SO20W
U$2: LOGO-SFENEW; SFE-NEW-WEBLOGO

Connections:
unnamed: JP1.1, U$1.P$10
unnamed: JP1.2, U$1.P$9
unnamed: JP1.3, U$1.P$8
unnamed: JP1.4, U$1.P$7
unnamed: JP1.5, U$1.P$6
unnamed: JP1.6, U$1.P$5
unnamed: JP1.7, U$1.P$4
unnamed: JP1.8, U$1.P$3
unnamed: JP1.9, U$1.P$2
unnamed: JP1.10, U$1.P$1
unnamed: JP2.1, U$1.P$20
unnamed: JP2.2, U$1.P$19
unnamed: JP2.3, U$1.P$18
unnamed: JP2.4, U$1.P$17
unnamed: JP2.5, U$1.P$16
unnamed: JP2.6, U$1.P$15
unnamed: JP2.7, U$1.P$14
unnamed: JP2.8, U$1.P$13
unnamed: JP2.9, U$1.P$12
unnamed: JP2.10, U$1.P$11

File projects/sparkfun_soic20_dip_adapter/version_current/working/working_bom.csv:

"Id";"Designator";"Footprint";"Quantity";"Designation";"Supplier and ref";
1;"JP2,JP1";"1X10";2;"M100.1";;;
2;"U$1";"SO20W";1;"SOIC_20";;;
3;"U$2";"SFE-NEW-WEBLOGO";1;"LOGO-SFENEW";;;

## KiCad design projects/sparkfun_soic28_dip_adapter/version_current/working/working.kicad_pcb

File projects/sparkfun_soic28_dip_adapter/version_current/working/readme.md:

# SOIC28-DIP_Adapter by sparkfun  
This is a harvested standardized copy of a project from github.  
The original project can be found at:  
https://github.com/sparkfun/SOIC28-DIP_Adapter  
Please consult that link for additional, details, files, and license information.  
Note: It was auto harvested and if the original repo had more than one board file or anything out of the ordinary the files here are likely not representative.

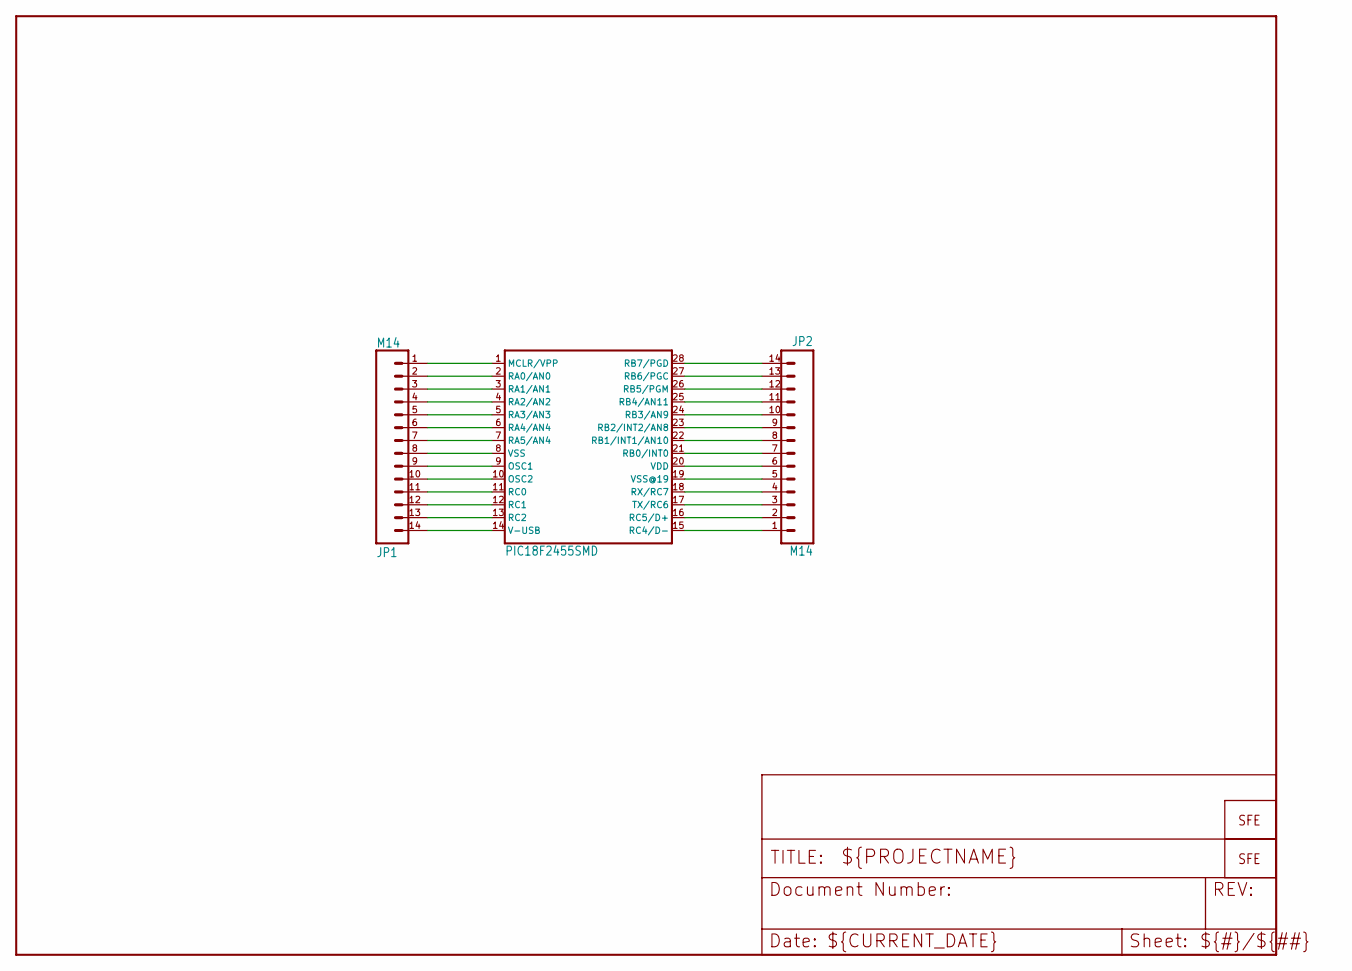
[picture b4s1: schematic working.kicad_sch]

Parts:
JP1, JP2: M14; 1X14
U$1: LOGO-SFESK; SFE-LOGO-FLAME
U$2: LOGO-SFENEW; SFE-NEW-WEBLOGO
U$3: PIC18F2455SMD; SO-28W

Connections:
unnamed: JP1.1, U$3.1 (MCLR/VPP)
unnamed: JP1.2, U$3.2 (RA0/AN0)
unnamed: JP1.3, U$3.3 (RA1/AN1)
unnamed: JP1.4, U$3.4 (RA2/AN2)
unnamed: JP1.5, U$3.5 (RA3/AN3)
unnamed: JP1.6, U$3.6 (RA4/AN4)
unnamed: JP1.7, U$3.7 (RA5/AN4)
unnamed: JP1.8, U$3.8 (VSS)
unnamed: JP1.9, U$3.9 (OSC1)
unnamed: JP1.10, U$3.10 (OSC2)
unnamed: JP1.11, U$3.11 (RC0)
unnamed: JP1.12, U$3.12 (RC1)
unnamed: JP1.13, U$3.13 (RC2)
unnamed: JP1.14, U$3.14 (V-USB)
unnamed: JP2.1, U$3.15 (RC4/D-)
unnamed: JP2.2, U$3.16 (RC5/D+)
unnamed: JP2.3, U$3.17 (TX/RC6)
unnamed: JP2.4, U$3.18 (RX/RC7)
unnamed: JP2.5, U$3.19 (VSS@19)
unnamed: JP2.6, U$3.20 (VDD)
unnamed: JP2.7, U$3.21 (RB0/INT0)
unnamed: JP2.8, U$3.22 (RB1/INT1/AN10)
unnamed: JP2.9, U$3.23 (RB2/INT2/AN8)
unnamed: JP2.10, U$3.24 (RB3/AN9)
unnamed: JP2.11, U$3.25 (RB4/AN11)
unnamed: JP2.12, U$3.26 (RB5/PGM)
unnamed: JP2.13, U$3.27 (RB6/PGC)
unnamed: JP2.14, U$3.28 (RB7/PGD)

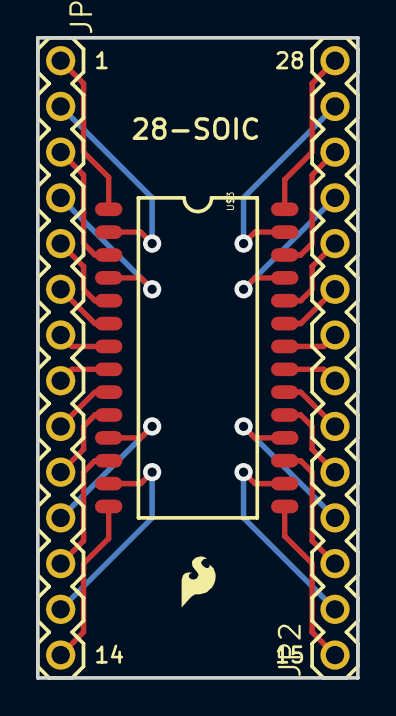
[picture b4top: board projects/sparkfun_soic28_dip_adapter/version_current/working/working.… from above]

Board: 2 copper layers, 17.8 x 35.6 mm, 5 parts (1 on the bottom side), 28 nets.

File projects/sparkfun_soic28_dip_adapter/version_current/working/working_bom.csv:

"Id";"Designator";"Footprint";"Quantity";"Designation";"Supplier and ref";
1;"JP2,JP1";"1X14";2;"M14";;;
2;"U$1";"SFE-LOGO-FLAME";1;"LOGO-SFESK";;;
3;"U$3";"SO-28W";1;"PIC18F2455SMD";;;
4;"U$2";"SFE-NEW-WEBLOGO";1;"LOGO-SFENEW";;;

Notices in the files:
projects/sparkfun_simultaneous_rfid_tag_reader/version_current/working/working.kicad_sch:
https://creativecommons.org/licenses/by-sa/4.0
Released under the Creative Commons
projects/sparkfun_sn74hc165_shift_in_breakout/version_current/working/working.kicad_sch:
http://creativecommons.org/licenses/by-sa/3.0
parts and their libraries:
Released under the Creative Commons Attribution Share-Alike 4.0 License
Released under the Creative Commons Attribution Share-Alike 3.0 License
